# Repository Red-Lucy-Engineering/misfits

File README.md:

# "Misfits" - e-Paper (smart)watch

Open hardware e-Paper based smartwatch, fully user programmable.

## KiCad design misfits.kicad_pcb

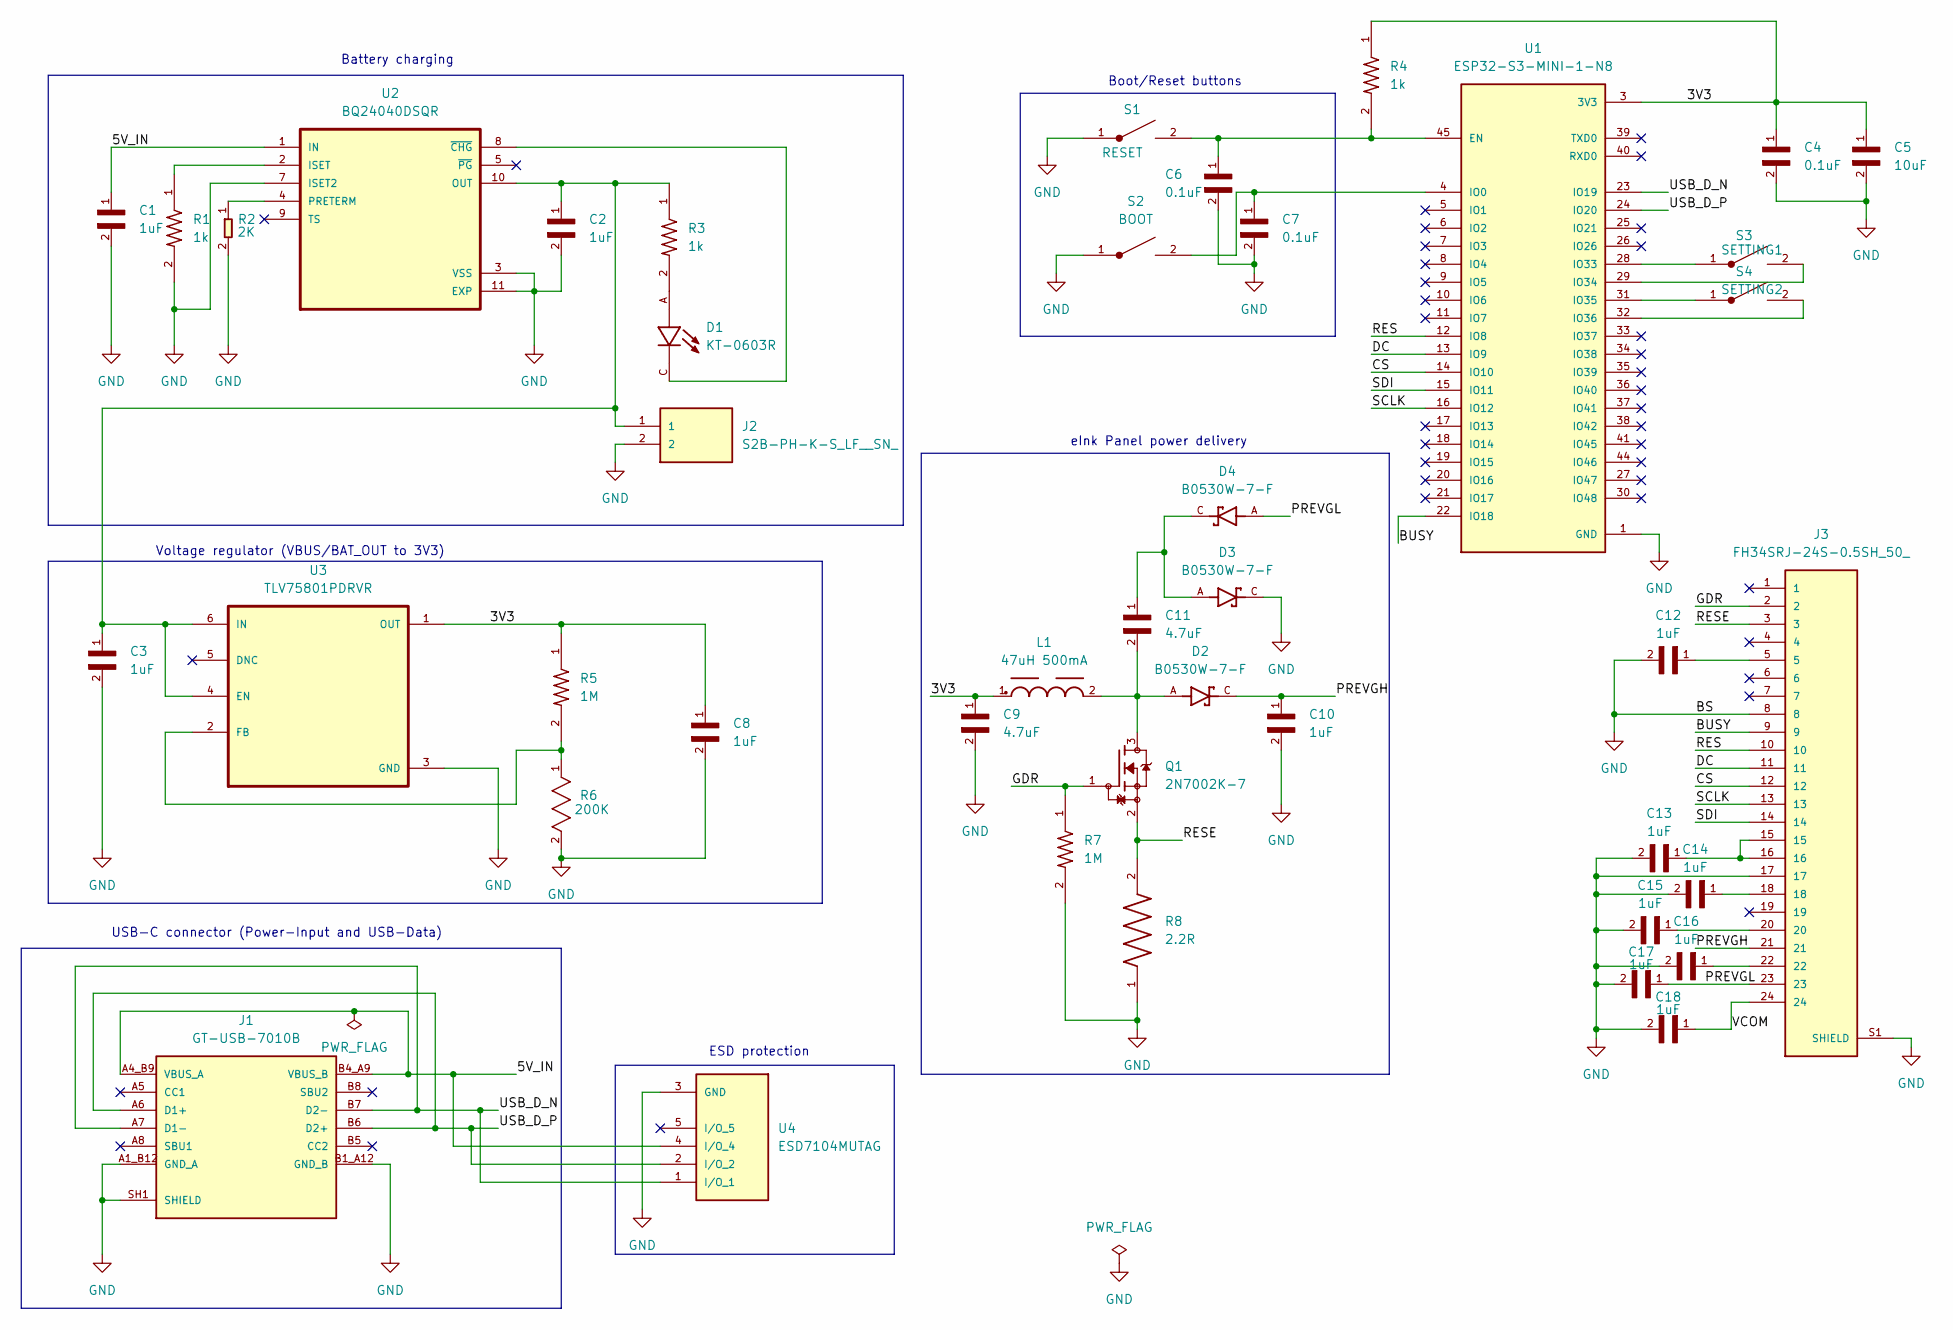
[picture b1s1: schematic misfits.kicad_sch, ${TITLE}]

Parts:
C1, C2, C3, C8, C10, C12, C13, C14, C15, C16, C17, C18: 1uF; CAPC1608X90N
C4, C6, C7: 0.1uF; CAPC1608X90N
C5: 10uF; CAPC1608X90N
C9, C11: 4.7uF; CAPC1608X90N
D1: KT-0603R; LED_KT-0603R; PARTREV 2013/01/24
D2, D3, D4: B0530W-7-F; SOD3715X145N; MPN C124188
J1: GT-USB-7010B; G-SWITCH_GT-USB-7010B; MPN C963217
J2: S2B-PH-K-S_LF__SN_; JST_S2B-PH-K-S_LF__SN_; MPN C173752
J3: FH34SRJ-24S-0.5SH_50_; HRS_FH34SRJ-24S-0.5SH_50_; MPN C324726
L1: 47uH 500mA; WE-TPC_4828; MPN C2046935
Q1: 2N7002K-7; SOT91P240X110-3N; MPN C85047
R1, R3, R4: 1k; RESC1607X60N
R2: 2K; R0603; MPN RC0603FR-072KL
R5, R7: 1M; RESC1607X60N
R6: 200K; RESC1608X60N; TOLERANCE ±1%; MPN RC0603FR-07200KL
R8: 2.2R; RESC1608X55N
S1: RESET; SW_EVP-AEDB2A; MPN C79150
S2: BOOT; SW_EVP-AEDB2A; MPN C79150
S3: SETTING1; SW_EVP-AEDB2A; MPN C79150
S4: SETTING2; SW_EVP-AEDB2A; MPN C79150
U1: ESP32-S3-MINI-1-N8; XCVR_ESP32-S3-MINI-1-N8
U2: BQ24040DSQR; SON40P200X200X80-11N; MPN C81080
U3: TLV75801PDRVR; SON65P200X200X80-7N; MPN C2876308
U4: ESD7104MUTAG; IC_ESD7104MUTAG; MPN C328026

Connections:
/3V3: C4.1, C5.1, C8.1, C9.1, L1.1, R4.1, R5.1, U1.3 (3V3), U3.1 (OUT)
/5V_IN: C1.1, J1.A4_B9 (VBUS_A), J1.B4_A9 (VBUS_B), U2.1 (IN), U4.4 (I/O_4)
/BUSY: J3.9, U1.22 (IO18)
/CS: J3.12, U1.14 (IO10)
/DC: J3.11, U1.13 (IO9)
/GDR: J3.2, Q1.1, R7.1
/PREVGH: C10.1, D2.C, J3.21
/PREVGL: C17.1, D4.A, J3.23
/RES: J3.10, U1.12 (IO8)
/RESE: J3.3, Q1.2, R8.2
/SCLK: J3.13, U1.16 (IO12)
/SDI: J3.14, U1.15 (IO11)
/USB_D_N: J1.A7 (D1-), J1.B7 (D2-), U1.23 (IO19), U4.1 (I/O_1)
/USB_D_P: J1.A6 (D1+), J1.B6 (D2+), U1.24 (IO20), U4.2 (I/O_2)
/VCOM: C18.1, J3.24
GND: C1.2, C2.2, C3.2, C4.2, C5.2, C6.2, C7.2, C8.2, C9.2, C10.2, C12.2, C13.2, C14.2, C15.2, C16.2, C17.2, C18.2, D3.C, J1.A1_B12 (GND_A), J1.B1_A12 (GND_B), J1.SH1 (SHIELD), J1.SH2 (SHIELD), J1.SH3 (SHIELD), J1.SH4 (SHIELD), J2.2, J3.8, J3.17, J3.S1 (SHIELD), J3.S2 (SHIELD), R1.2, R2.2, R6.2, R7.2, R8.1, S1.1, S1.1_1, S2.1, S2.1_1, U1.1 (GND), U1.2 (GND), U1.42 (GND), U1.43 (GND), U1.46 (GND), U1.47 (GND), U1.48 (GND), U1.49 (GND), U1.50 (GND), U1.51 (GND), U1.52 (GND), U1.53 (GND), U1.54 (GND), U1.55 (GND), U1.56 (GND), U1.57 (GND), U1.58 (GND), U1.59 (GND), U1.60 (GND), U1.61 (GND), U1.61_1 (GND), U1.61_2 (GND), U1.61_3 (GND), U1.61_4 (GND), U1.61_5 (GND), U1.61_6 (GND), U1.61_7 (GND), U1.61_8 (GND), U1.62 (GND), U1.63 (GND), U1.64 (GND), U1.65 (GND), U2.3 (VSS), U2.7 (ISET2), U2.11 (EXP), U3.3 (GND), U4.3 (GND), U4.8 (GND)
unnamed: C11.1, D3.A, D4.C
unnamed: C11.2, D2.A, L1.2, Q1.3
unnamed: C12.1, J3.5
unnamed: C13.1, J3.15, J3.16
unnamed: C14.1, J3.18
unnamed: C15.1, J3.20
unnamed: C16.1, J3.22
unnamed: D1.A, R3.2
unnamed: C6.1, R4.2, S1.2, U1.45 (EN)
unnamed: C7.1, S2.2, U1.4 (IO0)
unnamed: S3.1, S3.1_1, U1.28 (IO33)
unnamed: S3.2, U1.29 (IO34)
unnamed: S4.1, S4.1_1, U1.31 (IO35)
unnamed: S4.2, U1.32 (IO36)
unnamed: R1.1, U2.2 (ISET)
unnamed: C2.1, C3.1, J2.1, R3.1, U2.10 (OUT), U3.4 (EN), U3.6 (IN)
unnamed: R2.1, U2.4 (PRETERM)
unnamed: D1.C, U2.8 (~CHG)
unnamed: R5.2, R6.1, U3.2 (FB)

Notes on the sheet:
ESD protection
Boot/Reset buttons
USB-C connector (Power-Input and USB-Data)
Voltage regulator (VBUS/BAT_OUT to 3V3)
Battery charging
eInk Panel power delivery

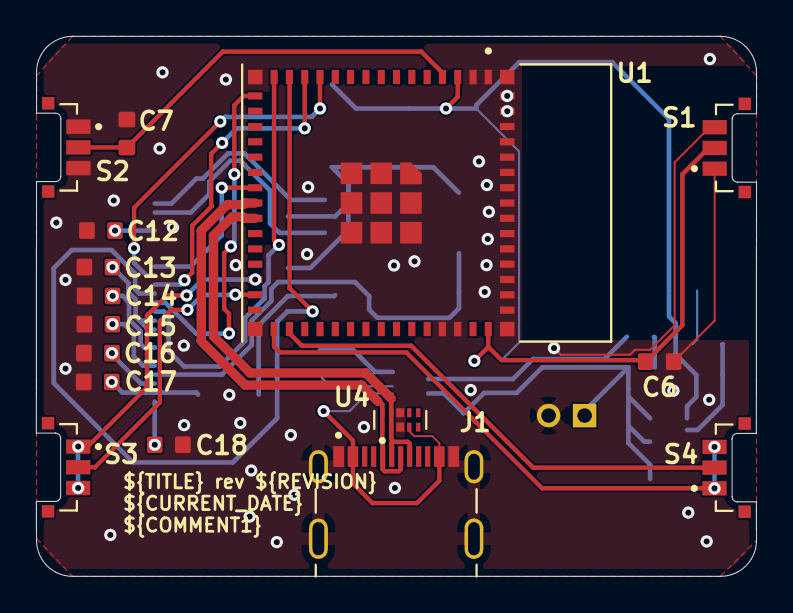
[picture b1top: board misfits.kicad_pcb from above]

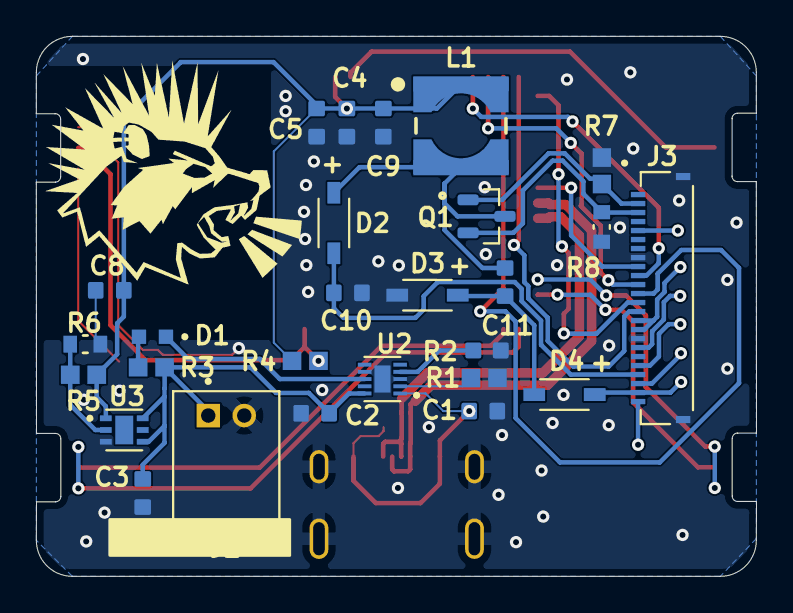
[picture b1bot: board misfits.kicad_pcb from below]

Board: 4 copper layers, 40.0 x 30.0 mm, 43 parts (27 on the bottom side), 35 nets.

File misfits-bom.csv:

Comment,Designator,Footprint
SETTING2,S4,SW_EVP-AEDB2A
SETTING1,S3,SW_EVP-AEDB2A
1.0uF,"C14,C17,C15,C12,C16,C13,C18,C8,C2,C3,C10,C1",CAPC1608X90N
ESD7104MUTAG,U4,IC_ESD7104MUTAG
ESP32-S3-MINI-1-N8,U1,XCVR_ESP32-S3-MINI-1-N8
BOOT,S2,SW_EVP-AEDB2A
0.10uF,"C7,C6,C4",CAPC1608X90N
RESET,S1,SW_EVP-AEDB2A
GT-USB-7010B,J1,G-SWITCH_GT-USB-7010B
1.0k,"R4,R1,R3",RESC1607X60N
10.0uF,C5,CAPC1608X90N
B0530W-7-F,"D3,D4,D2",SOD3715X145N
47uH 500mA,L1,WE-TPC_4828
FH34SRJ-24S-0.5SH_50_,J3,HRS_FH34SRJ-24S-0.5SH_50_
0.470uF,"C9,C11",CAPC1608X90N
2.20k,R8,RESC1608X55N
TLV75801PDRVR,U3,SON65P200X200X80-7N
200.0k,R6,RESC1608X60N
KT-0603R,D1,LED_KT-0603R
2N7002K-7,Q1,SOT91P240X110-3N
BQ24040DSQR,U2,SON40P200X200X80-11N
S2B-PH-K-S_LF__SN_,J2,JST_S2B-PH-K-S_LF__SN_
1.0M,"R7,R5",RESC1607X60N
2.0k,R2,R0603

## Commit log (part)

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2026-02-21 Add License
    This is the CERN-OHL-S, which seems to permit and enforce the exact
    things I need :)
2026-02-21 Disclaimer: WIP, not ready for use yet
    Which is also the reason there's a distinct lack of docs, descriptions,
    photos, etc. This is still early in the design process and the first PCB
    revision is in manufacturing right now (hasn't arrived yet).
2026-03-01 Add contribution guidelines
    The Starlight network agreed on a contribution policy
    (https://forge.starlightnet.work/Team/Meta/src/branch/master/Contribution-Policy-Agreement.md),
    which this project will use as well. Covers AI policy, as well as some
    important copyright holding stuff.
2026-03-01 Update README.md
    Add a bit more description and a screenshot. Needs a GIF of the finished
    hardware device, a couple photos, and more explanation on what the
    point is, and how to program the thing.
2026-03-01 Add TODO.md
    TODO-list for misfits Revision 2. A couple changes are necessary.
    A) The PCB assembly is way too expensive. Cost needs to be cut without
    sacrificing usability or quality, otherwise it's not worth it for end
    users. Panelizing is an option for example, which makes the cost per
    board cheaper.
    B) There are some improvements to be made. A vibration motor of some
2026-03-01 TODO.md: fix broken formatting
2026-03-07 Add TODO for fixing oopsie daisy
    🙂🙂🙂🙂🙂🙂🙂🙂🙂🙂🙂🙂
2026-03-07 Add TODO
2026-03-11 Update todos
    since rev1 is a brick now, i might as well do rev2, since i can't write
    the code for that thing anyways rn.
2026-03-11 Fix gnd copper fill zones and esd protection placement
    ESD protection placement was wrong, and the default "remove islands"
    crap from KiCAD (why the fuck is *that* the default?) failed to provide
    proper ground connections. These issues have been fixed now.
2026-03-11 Update TODO.md
    See previous commit
2026-03-12 Connect copper zone islands with GND vias and double check GND pins
    Most copper zone islands have been connected with through-hole vias. The
    islands that are too small or have traces running through on the other
    side aren't connected, but since they aren't connected to any ground
    pins, this shouldn't be too big of an issue.
2026-03-14 Fix DRC errors
    Assign pins missing from schematic properly, etc.
2026-03-14 Revision 2
    Revision 2 ready.
    Gerbers, Pick and place file and BoM generated and modified for JLCPCB
2026-03-28 init source directory
2026-03-28 src: misfits.c: start with basic initialization
    Main function lives here. Adds the initialization logic that has been
    implemented so far.
2026-03-28 src: add watch-timer.h
    Adds a header for dealing with timer-related configurations and
    callbacks called "watch-timer.h".
    A couple definitions and a skeleton for a callback function currently
    live here.
    This timer functionality will be the way this watch will keep time, and
    based on the callback, the watch is supposed to update the epaper
2026-03-28 src: add common-defs.h
    Add a general purpose header file for common definitions and such called
    "common-defs.h".
    Currently, there's only the definition for TAG, since this is used
    across all files whenever there is a logging statement. Similar things
    should also go in here.
2026-03-28 src: add header for ePaper display handling
    Adds a header for ePaper display handling called "epd-spi.h".
    Currently, only some pin definitions and basic data sending functions
    live here.
2026-03-28 src: epd-spi.h: fix data handover in epd_send_data transaction
2026-03-28 src: CMakeLists.txt: Add used driver libs from ESP-IDF
2026-03-28 src: misfits.c: fix datatype on return variable
    Technically, it's the same, but it's cleaner setting it to the exact
    same datatype. Internally, esp_err_t might be int, but it's imho a bit
    clearer what that int is supposed to be when it's set the way Espressif
    intended.
2026-03-28 src: epd-spi.h: initialization logic
    The display, like any other piece of hardware, needs to be properly
    initalized. This provides the basic initalisation needed after boot of
    the MCU.
2026-03-28 src: epd-spi.h: Check busy flag when appropriate
2026-03-28 src: epd-spi.c/h: split implementation and declaration
    Helps with compiling speed, or so I've heard...
2026-03-28 src: restructuring
    Code had to be restructured, so it gets properly compiled by idf
2026-03-29 src: watch-timer.h: split implementation and declaration
2026-03-29 src: misfits.c: Correct order of operations
    Since timer_init() also registers and activates the callback for keeping
    time and updating the screen every minute, the display already needs to
    be initialized (call to epd_init()).
2026-03-29 src: epd-spi.c/h: add "static" for locally used functions
    Some functions are to be used only locally within epd-spi, and shouldn't
    be exposed to whoever is using the header externally. the "static"
    prefix provides this.
2026-03-29 src: epd-spi: implement display update routine
    Introduces the function epd_update_display(), which allows for drawing a
    whole display buffer to the screen, for convenience.
    There are multiple steps involved into drawing physically on the
    screen, which is taken care of by epd_update_display():
    1. Send command CMD_WRITE_RAM
    2. Writes the user-defined data to display RAM
2026-03-29 src: epd-spi: epd_update_display: fix "size" comment
2026-03-29 src: epd-spi/watch-timer: change static to static inline
2026-03-30 Added rendering routines, shell code, and a sketch for a simulator.
2026-03-30 Attempting a new structure, so we can divide concerns better.
2026-03-30 src: fix: CMake build errors due to changed folder structure
    Fixes the CMake/idf build errors that result from moving around the esp
    code.
    It also adds the dependencies to esp/CMakeLists.txt that I should've
    added from the getgo (sorry :') )
2026-03-30 Attempting to decouple the shell from the main code, backend stuff, added a filesystem API, might need revising.
2026-03-30 src: shared: shell: supply typedef for esp_err_t
2026-03-30 src: esp: misfits: write black to display to test it
    I still need to test if the display itself works, or if any of my
    low-level routines function properly.
2026-03-30 Preliminary scripting support, evilware incorporated.
2026-03-30 Oops.
2026-03-30 MF file format.
2026-03-31 src: esp: Error handling
2026-03-31 esp: misc: Better logging
    I was unable to trace an issue where the ESP32 module hangs, due to
    shitty logging.
2026-04-01 Updated format description.
2026-04-01 what was i thinking...
2026-04-01 Here we go.
2026-04-01 Add small structure file so we can navigate this mess without getting lost lol
2026-04-01 Last changes before bed.
2026-04-01 src: epd-spi: add debug logging statements
2026-04-01 src: epd-spi: Fix Busy-Flag check
    We need to wait for the busy flag properly.
2026-04-01 src: epd-spi: more logging
    log me daddy~
2026-04-01 src: epd-spi: epd_update_display: Fix loop exit
    need a proper real exit condition for when data fails to get sent to the
    display
2026-04-01 src: misfits: reset display to white after a second
2026-04-01 src: epd-spi: epd_update_display: add delay so the scheduler can schedule
    Pet the doggy :3
2026-04-02 src: epd-spi: epd_update_display: send softstart command
    The display ICU requires the softstart command to be sent after writing
    to ram, according to the datasheet
    (https://files.seeedstudio.com/wiki/Other_Display/154-epaper/GDEY0154D67.pdf)
    page 28.
2026-04-02 src: epd-spi: epd_update_display: remove logging and delay from loop
    It slows down the writing process too much, to the point where it causes
    issues for the display MCU.
2026-04-06 src: esp: misc debug changes
    Current state of the lower level code.
    Changes to the logging statements to avoid douple newline, using bulk
    data transfer via SPI, etc etc.
    Since the main issue the display isn't updating is actually R8's wrong
    value (2.2k instead of the correct 2.2R), these have to be tested once
    the prototype has been physically corrected
2026-04-06 add .gitignore
2026-04-10 misc: Proper contribution guidelines
2026-04-11 chematics: correct R8 to 2.2 Ohms
